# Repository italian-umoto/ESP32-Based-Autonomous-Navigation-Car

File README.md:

# ESP32-Based-Autonomous-Navigation-Car

## About the Project

ESP32-Based-Autonomous-Navigation-Car is a group project created for **Junior Design Project at Tufts University**. Our goal was to **create a fully autonomous robot that is capable of traversing a track without human intervention and learn about the desinging process on a more in-depth level**.

## Features

* [Feature 1]
* [Feature 2]
* [Feature 3]

## Technologies Used

This project was built using:

* **ESP32** – 
* **Git & GitHub** – version control and team collaboration

## Team Members

This project was developed by:

* **[Name]** – [role]

## How It Works
WebSocket commands:

```text
MAGICSMOKE67 set: STATE=7,1  (start/restart solo bot #1)
MAGICSMOKE67 set: STATE=7,2  (start/restart solo bot #2)
MAGICSMOKE67 set: STATE=0,0  (stop and return to manual mode)
```

## Project Structure

```text
[project-folder]/
├── [folder]/
├── [folder]/
├── [file]
├── [file]
└── README.md
```

## Challenges & What We Learned

Throughout this project, our team gained experience 

## Future Improvements

If we continued developing this project, we would like to:

* [Future improvement]
* [Future improvement]
* [Future improvement]

## Acknowledgments

We would like to thank **John Doe** for providing the guidance and resources that helped us complete this project.

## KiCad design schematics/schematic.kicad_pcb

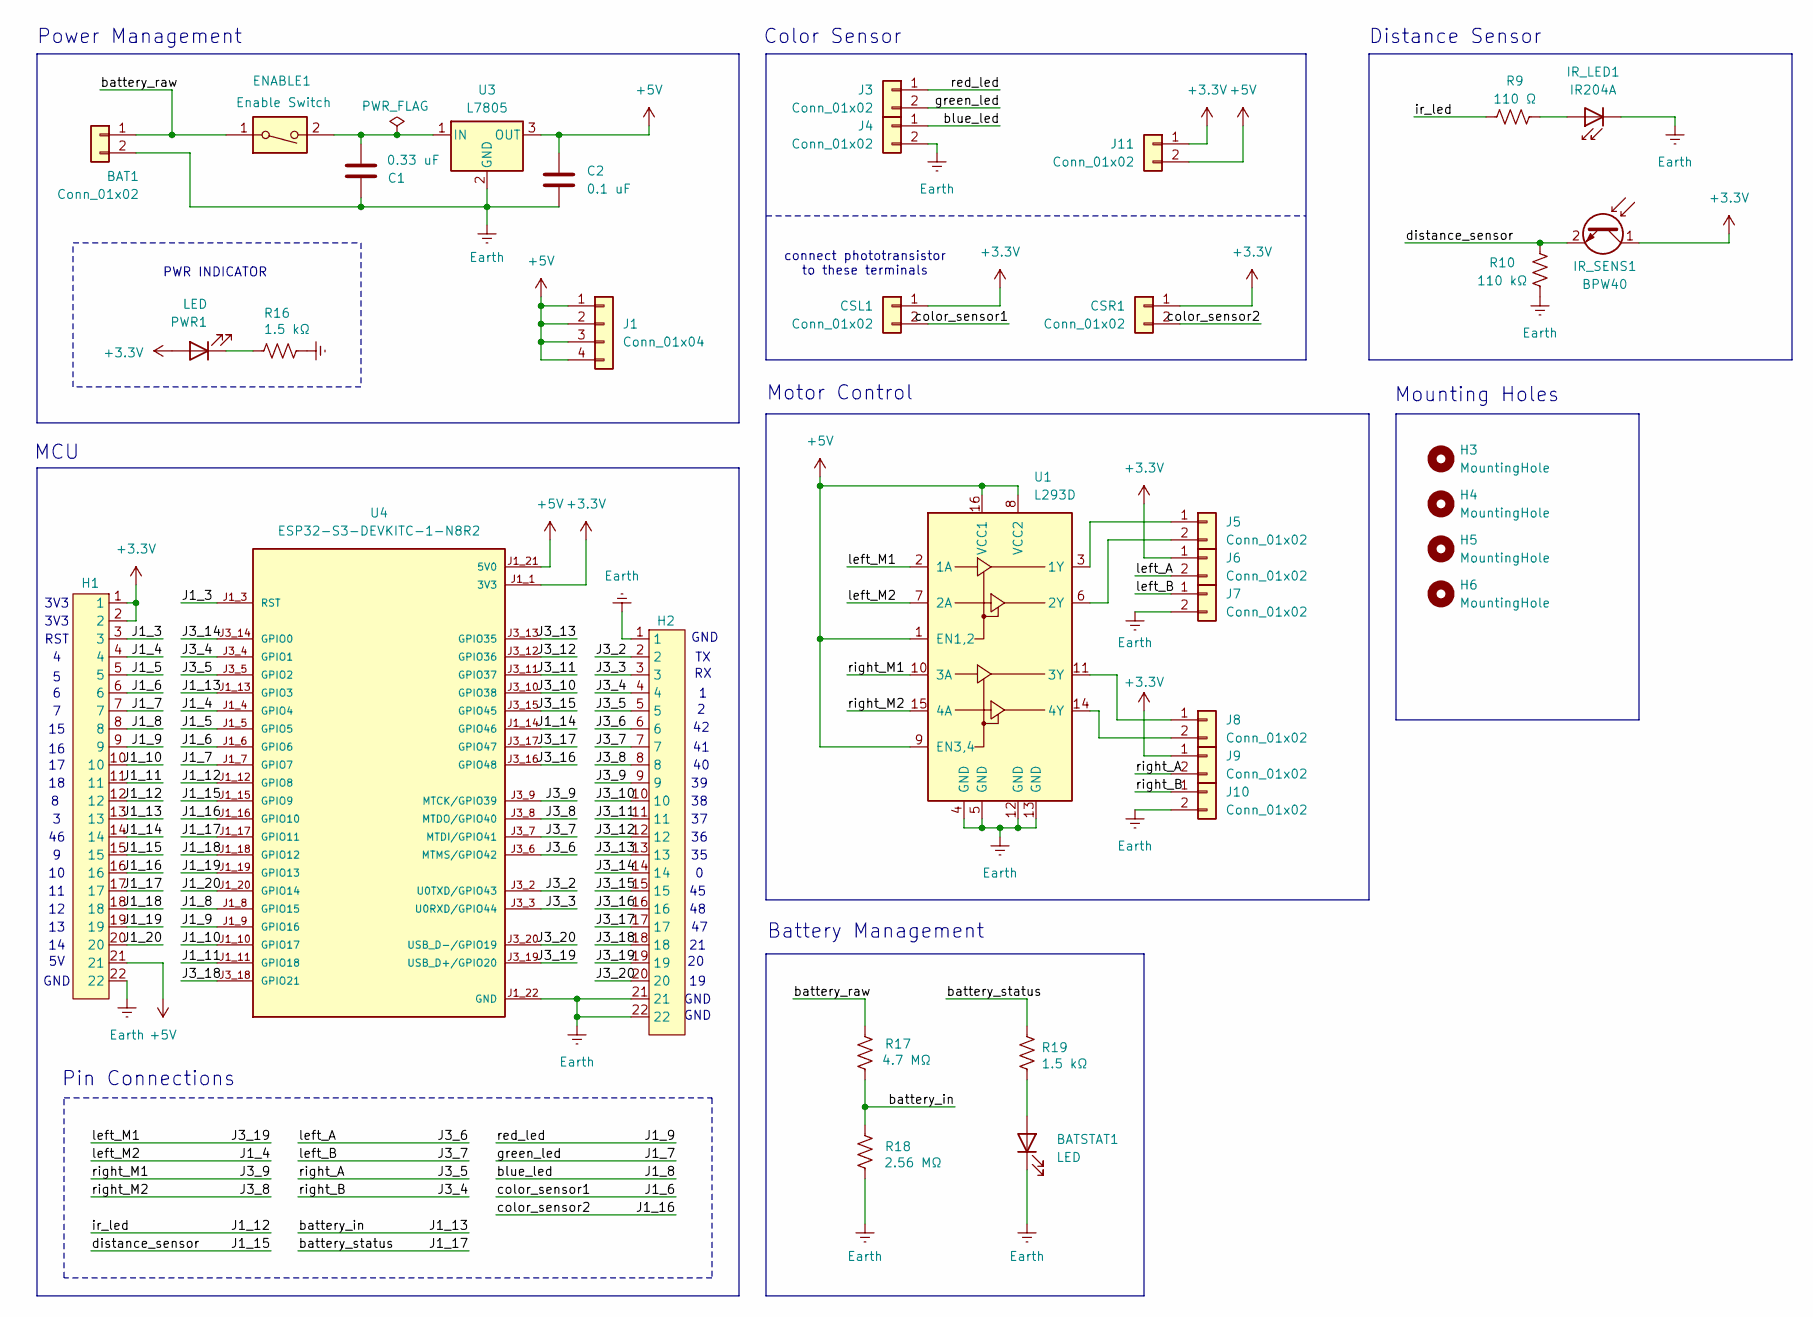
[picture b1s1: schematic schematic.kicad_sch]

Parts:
BAT1: Conn_01x02; CONN2_282836-2_TEC
BATSTAT1: LED; LED_D5.0mm
C1: 0.33 uF; C_0603_1608Metric
C2: 0.1 uF; C_0603_1608Metric
CSL1: Conn_01x02; CONN2_282836-2_TEC
CSR1: Conn_01x02; CONN2_282836-2_TEC
ENABLE1: Enable Switch; Single Position DIP Switch
H1, H2: PinHeader_1x22_P2.54mm_Vertical
H3, H4, H5, H6: MountingHole; MountingHole_2.7mm_M2.5
IR_LED1: IR204A; LED_D3.0mm_IRBlack
IR_SENS1: BPW40; LED_D5.0mm
J1: Conn_01x04; PinHeader_1x04_P2.54mm_Vertical
J3, J4, J5, J6, J7, J8, J9, J10, J11: Conn_01x02; CONN2_282836-2_TEC
PWR1: LED; LED_D5.0mm
R9: 110 Ω; R_0603_1608Metric
R10: 110 kΩ; R_0603_1608Metric
R16, R19: 1.5 kΩ; R_0603_1608Metric
R17: 4.7 MΩ; R_Box_L14.0mm_W5.0mm_P9.00mm
R18: 2.56 MΩ; R_Box_L14.0mm_W5.0mm_P9.00mm
U1: L293D; DIP-16_W7.62mm
U3: L7805; TO-220-3_Vertical
U4: ESP32-S3-DEVKITC-1-N8R2; XCVR_ESP32-S3-DEVKITC-1-N8R2; PARTREV V1

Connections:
+3.3V: CSL1.1, CSR1.1, H1.1, H1.2, IR_SENS1.1 (C), J6.1, J9.1, J11.1, PWR1.2 (A), U4.J1_1 (3V3), U4.J1_2 (3V3)
+5V: C2.1, H1.21, J1.1, J1.2, J1.3, J1.4, J11.2, U1.1 (EN1,2), U1.8 (VCC2), U1.9 (EN3,4), U1.16 (VCC1), U3.3 (OUT), U4.J1_21 (5V0)
/J1_3: H1.3, U4.J1_3 (RST)
/J1_4: H1.4, U1.7 (2A), U4.J1_4 (GPIO4)
/J1_5: H1.5, U4.J1_5 (GPIO5)
/J1_6: CSL1.2, H1.6, U4.J1_6 (GPIO6)
/J1_7: H1.7, J3.2, U4.J1_7 (GPIO7)
/J1_8: H1.8, J4.1, U4.J1_8 (GPIO15)
/J1_9: H1.9, J3.1, U4.J1_9 (GPIO16)
/J1_10: H1.10, U4.J1_10 (GPIO17)
/J1_11: H1.11, U4.J1_11 (GPIO18)
/J1_12: H1.12, R9.1, U4.J1_12 (GPIO8)
/J1_13: H1.13, R17.1, R18.2, U4.J1_13 (GPIO3)
/J1_14: H1.14, U4.J1_14 (GPIO46)
/J1_15: H1.15, IR_SENS1.2 (E), R10.2, U4.J1_15 (GPIO9)
/J1_16: CSR1.2, H1.16, U4.J1_16 (GPIO10)
/J1_17: H1.17, R19.1, U4.J1_17 (GPIO11)
/J1_18: H1.18, U4.J1_18 (GPIO12)
/J1_19: H1.19, U4.J1_19 (GPIO13)
/J1_20: H1.20, U4.J1_20 (GPIO14)
/J3_2: H2.2, U4.J3_2 (U0TXD/GPIO43)
/J3_3: H2.3, U4.J3_3 (U0RXD/GPIO44)
/J3_4: H2.4, J10.1, U4.J3_4 (GPIO1)
/J3_5: H2.5, J9.2, U4.J3_5 (GPIO2)
/J3_6: H2.6, J6.2, U4.J3_6 (MTMS/GPIO42)
/J3_7: H2.7, J7.1, U4.J3_7 (MTDI/GPIO41)
/J3_8: H2.8, U1.15 (4A), U4.J3_8 (MTDO/GPIO40)
/J3_9: H2.9, U1.10 (3A), U4.J3_9 (MTCK/GPIO39)
/J3_10: H2.10, U4.J3_10 (GPIO38)
/J3_11: H2.11, U4.J3_11 (GPIO37)
/J3_12: H2.12, U4.J3_12 (GPIO36)
/J3_13: H2.13, U4.J3_13 (GPIO35)
/J3_14: H2.14, U4.J3_14 (GPIO0)
/J3_15: H2.15, U4.J3_15 (GPIO45)
/J3_16: H2.16, U4.J3_16 (GPIO48)
/J3_17: H2.17, U4.J3_17 (GPIO47)
/J3_18: H2.18, U4.J3_18 (GPIO21)
/J3_19: H2.19, U1.2 (1A), U4.J3_19 (USB_D+/GPIO20)
/J3_20: H2.20, U4.J3_20 (USB_D-/GPIO19)
/battery_raw: BAT1.1, ENABLE1.1, R17.2
Earth: BAT1.2, BATSTAT1.1 (K), C1.1, C2.2, H1.22, H2.1, H2.21, H2.22, IR_LED1.1 (K), J4.2, J7.2, J10.2, R10.1, R16.2, R18.1, U1.4 (GND), U1.5 (GND), U1.12 (GND), U1.13 (GND), U3.2 (GND), U4.J1_22 (GND), U4.J3_1 (GND), U4.J3_21 (GND), U4.J3_22 (GND)
unnamed: BATSTAT1.2 (A), R19.2
unnamed: IR_LED1.2 (A), R9.2
unnamed: J5.1, U1.3 (1Y)
unnamed: J5.2, U1.6 (2Y)
unnamed: J8.1, U1.11 (3Y)
unnamed: J8.2, U1.14 (4Y)
unnamed: PWR1.1 (K), R16.1
unnamed: C1.2, ENABLE1.2, U3.1 (IN)

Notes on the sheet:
Motor Control
Mounting Holes
MCU
GND
Pin Connections
Color Sensor
connect phototransistor to these terminals
PWR INDICATOR
RST
Battery Management
Distance Sensor
3V3
Power Management

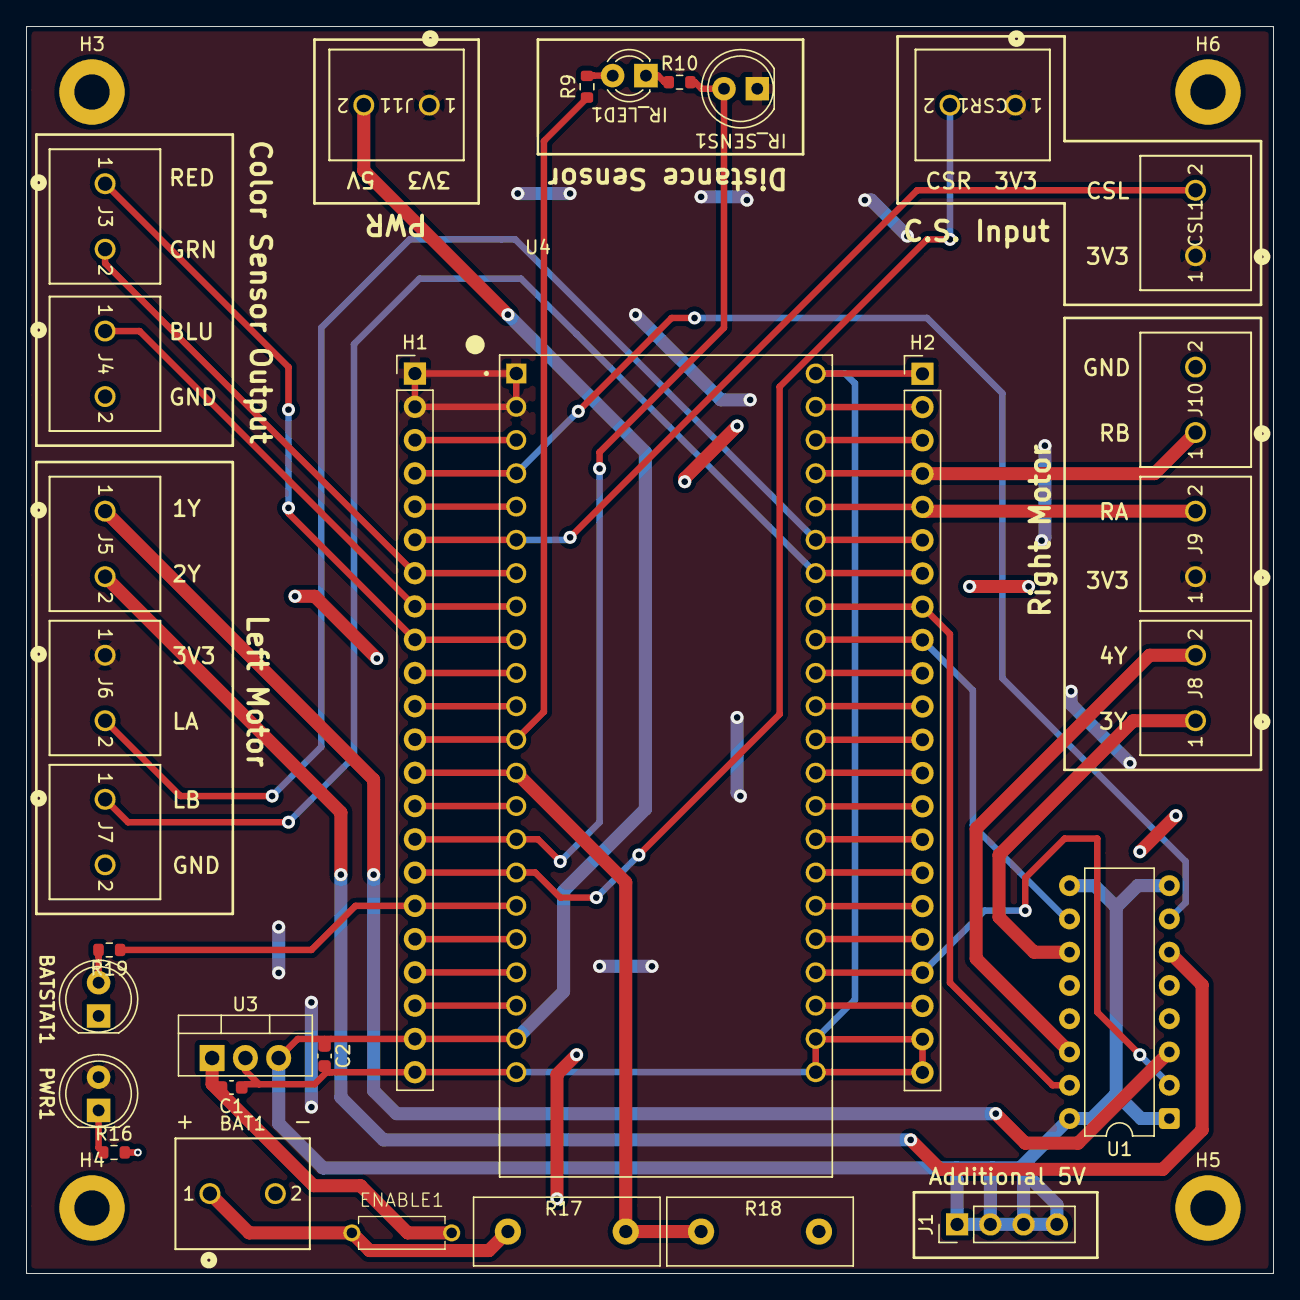
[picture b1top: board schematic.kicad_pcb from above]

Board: 2 copper layers, 95.2 x 95.2 mm, 35 parts (0 on the bottom side), 49 nets.
